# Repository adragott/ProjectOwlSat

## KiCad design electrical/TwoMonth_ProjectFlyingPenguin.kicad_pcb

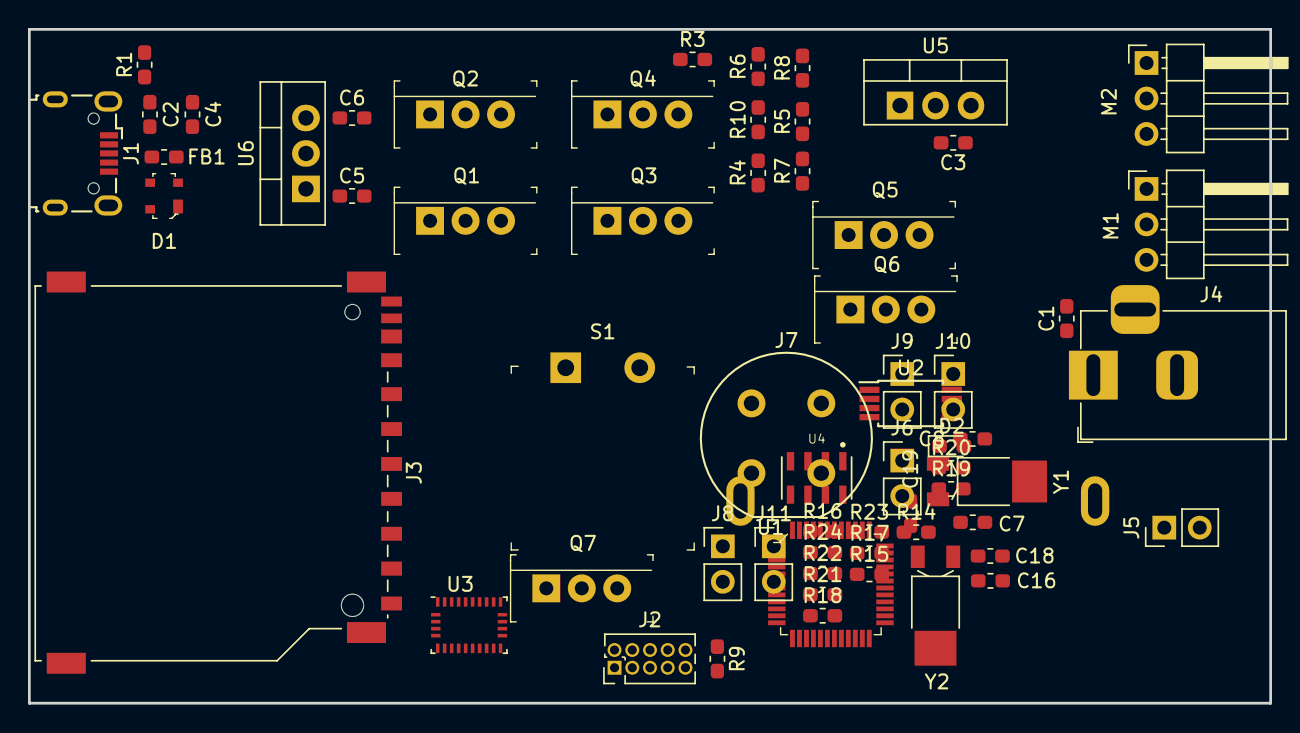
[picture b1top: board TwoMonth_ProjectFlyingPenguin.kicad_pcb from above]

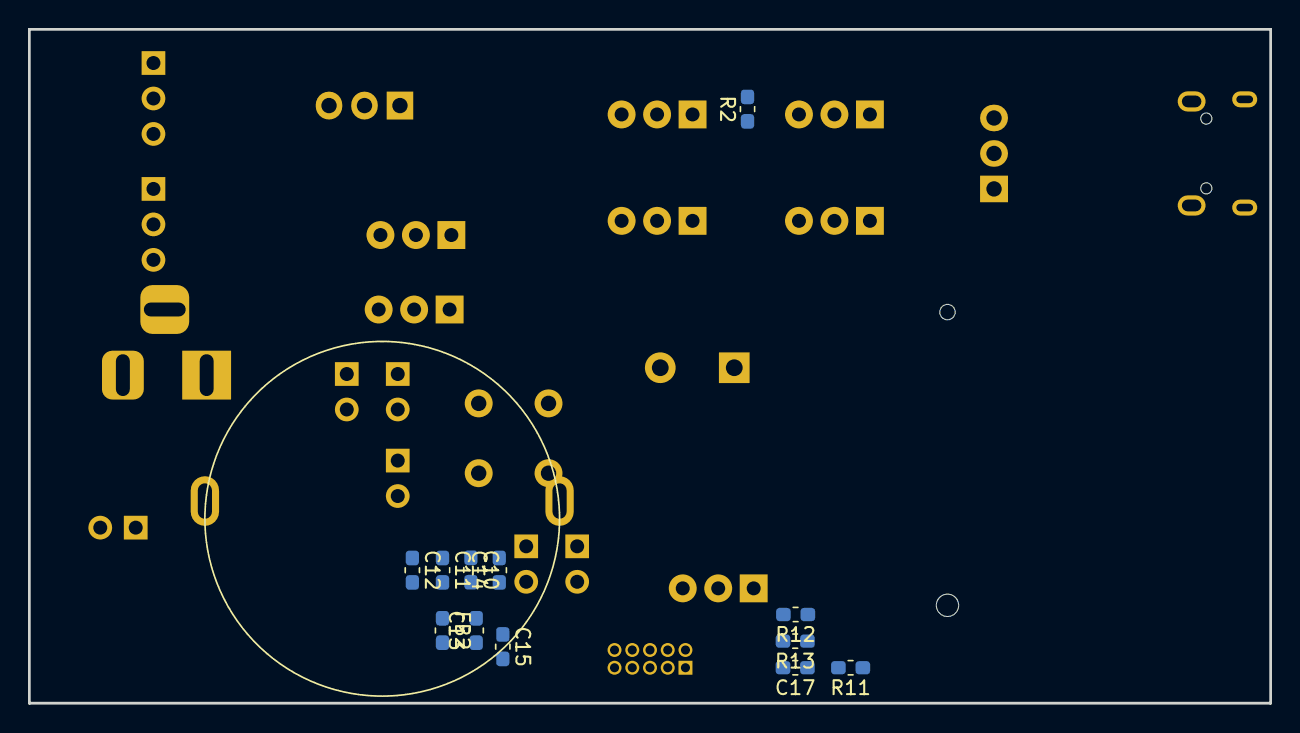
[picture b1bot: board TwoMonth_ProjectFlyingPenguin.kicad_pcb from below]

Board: 2 copper layers, 88.9 x 48.3 mm, 76 parts (13 on the bottom side), 49 nets, no tracks yet.

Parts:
C1: 0.47uF; C_0603_1608Metric_Pad1.05x0.95mm_HandSolder
C2, C4: 1nF; C_0603_1608Metric_Pad1.05x0.95mm_HandSolder
C3: 22uF; C_0603_1608Metric_Pad1.05x0.95mm_HandSolder
C5, C6, C14: 10uF; C_0603_1608Metric_Pad1.05x0.95mm_HandSolder
C7, C8: 6.8pF; C_0603_1608Metric_Pad1.05x0.95mm_HandSolder
C9: 4F; SuperCap
C10, C12, C13, C15: 100nF; C_0603_1608Metric_Pad1.05x0.95mm_HandSolder
C11: 1uF; C_0603_1608Metric_Pad1.05x0.95mm_HandSolder
C16, C17: 0.1uF; C_0603_1608Metric_Pad1.05x0.95mm_HandSolder
C18, C19: 22pF; C_0603_1608Metric_Pad1.05x0.95mm_HandSolder
D1: PRTR5V0U2X_215; TO-253-4
D2: POWER_LED; LED_0603_1608Metric_Pad1.05x0.95mm_HandSolder
FB1, FB2: 470 @ 100Mhz (BLM18PG471SN1); C_0603_1608Metric_Pad1.05x0.95mm_HandSolder
J1: USB_B_Micro; USB_Micro-B_Wuerth_629105150521
J2: Conn_ARM_JTAG_SWD_10; PinHeader_2x05_P1.27mm_Vertical
J3: Micro_SD_Card_Det; SD_TE_2041021
J4: Battery_Barrel_Jack; BarrelJack_Horizontal
J5: Hotwire; PinHeader_1x02_P2.54mm_Vertical
J6: FLIGHT_LED_0; PinHeader_1x02_P2.54mm_Vertical
J7: SS0750301F020P1A; Push_E-Switch_KS01Q01
J8: FLIGHT_LED_1; PinHeader_1x02_P2.54mm_Vertical
J9: FLIGHT_LED_2; PinHeader_1x02_P2.54mm_Vertical
J10: NTCLE100E3103JB0 (Therm 1); PinHeader_1x02_P2.54mm_Vertical
J11: NTCLE100E3103JB0 (Therm 2); PinHeader_1x02_P2.54mm_Vertical
M1: Elevator_Servo; PinHeader_1x03_P2.54mm_Horizontal
M2: Fin_Servo; PinHeader_1x03_P2.54mm_Horizontal
Q1: PFETDefaultA; TO-220-3
Q2: PFETAltA; TO-220-3
Q3: PFETDefaultB; TO-220-3
Q4: PFETAltB; TO-220-3
Q5: FQP27P06; TO-220-3
Q6, Q7: FQP30N06L; TO-220-3
R1, R2: 200K; R_0603_1608Metric_Pad1.05x0.95mm_HandSolder
R3: 100K; R_0603_1608Metric_Pad1.05x0.95mm_HandSolder
R4, R5, R6, R7, R8, R10, R11, R12, R13, R21: 10k; R_0603_1608Metric_Pad1.05x0.95mm_HandSolder
R9: 1k; R_0603_1608Metric_Pad1.05x0.95mm_HandSolder
R14: 330; R_0603_1608Metric_Pad1.05x0.95mm_HandSolder
R15, R17, R18: 25; R_0603_1608Metric_Pad1.05x0.95mm_HandSolder
R16: 4.7k; R_0603_1608Metric_Pad1.05x0.95mm_HandSolder
R19: 100k; R_0603_1608Metric_Pad1.05x0.95mm_HandSolder
R20: 39; R_0603_1608Metric_Pad1.05x0.95mm_HandSolder
R22: 3.2k; R_0603_1608Metric_Pad1.05x0.95mm_HandSolder
R23, R24: 20k; R_0603_1608Metric_Pad1.05x0.95mm_HandSolder
S1: ~RESET_BUTTON; PushButton_12x12mm_THT_GPTS203211B
U1: ATSAMD21G18A-AUT; TQFP-48_7x7mm
U2: AT25SF081-XMHD-X; TSSOP-8_4.4x3mm_P0.65mm
U3: BNO055; LGA-28_5.2x3.8mm_P0.5mm
U4: MS561101BA03-50; SON125P500X300X100-8N
U5: LM2940_TO220; TO-220-3_Vertical
U6: MIC29310; TO-220-3_Vertical
Y1, Y2: 32.768Khz; Crystal_SMD_MicroCrystal_MS1V-T1K

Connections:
+3V3: C6.1, C10.1, C11.1, C12.1, C13.1, C16.1, D2.2, FB2.1, J2.1, J3.4, R4.2, R5.2, R7.1, R8.1, R9.1, R10.2, R15.2, R17.2, R18.2, R19.1, R23.1, R24.1, U1.17, U1.36, U1.43, U1.44, U2.8, U3.3, U3.4, U3.28, U4.1, U6.3
+5V: C5.1, M1.2, M2.2, Q3.2, Q4.2, Q5.3, U6.1
/BATTV_ADC0: R21.2, R22.1, U1.3
/BNO_XIN32: C19.2, U3.27, Y2.1
/BNO_XOUT32: C18.1, U3.26, Y2.2
/FLIGHT_LED_CTRL: Q7.1, R16.2, U1.37
/FLIGHT_LED_DRAIN: J6.2, J8.2, J9.2, Q7.2
/Hotwire_GPO: Q5.1, Q6.1, R6.1, U1.16
/PWM0_FIN: M2.1, U1.19
/PWM1_ELEV: M1.1, U1.15
/RAW_BATTERY_V+: C1.1, J7.1, R21.1, U5.1
/SCL: R8.2, U1.14, U3.19, U4.8
/SDA: R7.2, U1.13, U3.20, U4.7
/SPI0_MOSI: J3.3, J3.7, U1.11, U2.2, U2.5
/SPI0_SCK: J3.5, U1.12, U2.6
/SPI0_SS_0: U1.10, U2.1
/SPI0_SS_1: J3.2, U1.21
/SWCLK: J2.4, R9.2, U1.45
/SWDIO: J2.2, U1.46
/THERM1_ADC1: J10.2, R23.2, U1.4
/THERM2_ADC2: J11.2, R24.2, U1.7
/USB_5V+: C4.1, FB1.1, Q1.2, Q2.1, Q4.1, R1.1
/USB_D+: D1.2, J1.3, U1.34
/USB_D-: D1.3, J1.2, U1.33
/VBUS: C2.1, D1.4, FB1.2, J1.1
/VDD_ANA: C14.1, C15.1, FB2.2, U1.6
/XIN32: C7.2, U1.1, Y1.1
/XOUT32: C8.1, U1.2, Y1.2
/uSD_CARD_DET: J3.10, U1.22
/~SYS_RESET: J2.10, R19.2, R20.1, U1.40, U3.11
GND: C1.2, C2.2, C3.2, C4.2, C5.2, C6.2, C7.1, C8.2, C9.2, C10.2, C11.2, C12.2, C13.2, C14.2, C15.2, C16.2, C17.2, C18.2, C19.1, D1.1, J1.5, J1.6, J2.3, J2.5, J2.9, J3.6, J3.11, J4.2, J4.3, J10.1, J11.1, M1.3, M2.3, Q6.3, Q7.3, R1.2, R2.2, R3.2, R6.2, R11.2, R12.2, R13.2, R14.2, R16.1, R22.2, S1.2, U1.5, U1.18, U1.35, U1.42, U2.4, U3.2, U3.10, U3.15, U3.16, U3.18, U3.25, U4.3, U5.2, U6.2, Y1.3, Y2.3
unnamed: C3.1, Q2.2, R2.1, U5.3
unnamed: C9.1, J5.1, Q5.2
unnamed: C17.1, U3.9
unnamed: D2.1, R14.1
unnamed: J4.1, J7.3
unnamed: J5.2, Q6.2
unnamed: J6.1, R15.1
unnamed: J8.1, R17.1
unnamed: J9.1, R18.1
unnamed: Q1.1, Q2.3, Q3.1, Q4.3, R3.1
unnamed: Q1.3, Q3.3
unnamed: R4.1, U2.3
unnamed: R5.1, U2.7
unnamed: R10.1, U4.2, U4.4, U4.5
unnamed: R11.1, U3.17
unnamed: R12.1, U3.5
unnamed: R13.1, U3.6
unnamed: R20.2, S1.1

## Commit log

2019-10-06 init
2019-10-06 added software readme
2019-10-06 Added power part of schematic. doing mcu now
2019-10-06 Finished placing parts. need to route tracks
2019-10-07 Added software stuff
2019-10-07 Finished schematic I think. Cant find part for rbf switch
2019-10-10 Added more project files for owlsat software
2019-10-14 added cap charge and discharge script
2019-10-18 added i2c stuff
2019-10-29 i2c stuff
2019-10-29 added usb stuff
2019-10-30 recreating project due to asf failure
2019-10-31 somehow shit works barely sorta?
2019-10-31 project remade, usb working, usart working
